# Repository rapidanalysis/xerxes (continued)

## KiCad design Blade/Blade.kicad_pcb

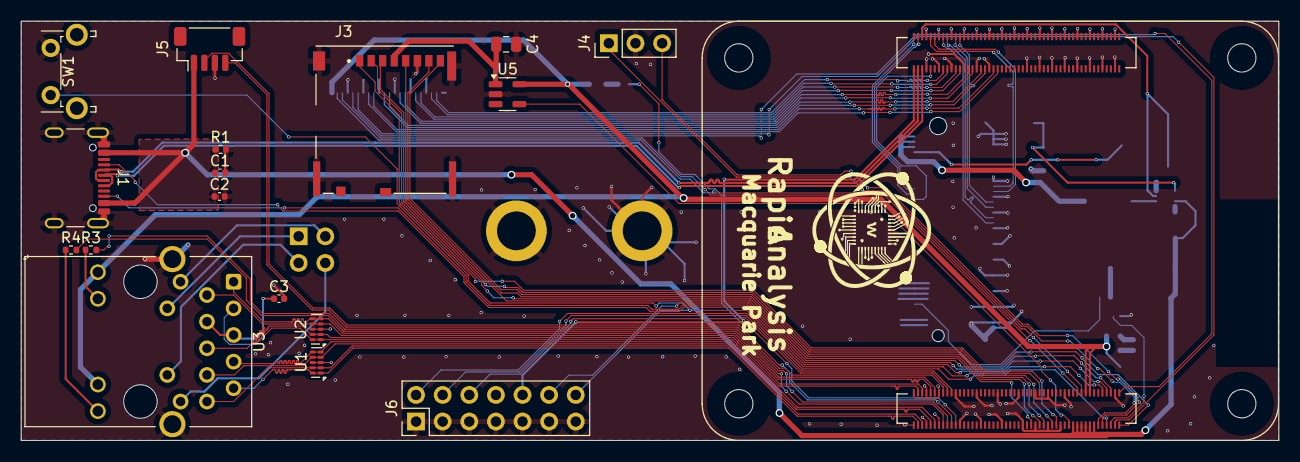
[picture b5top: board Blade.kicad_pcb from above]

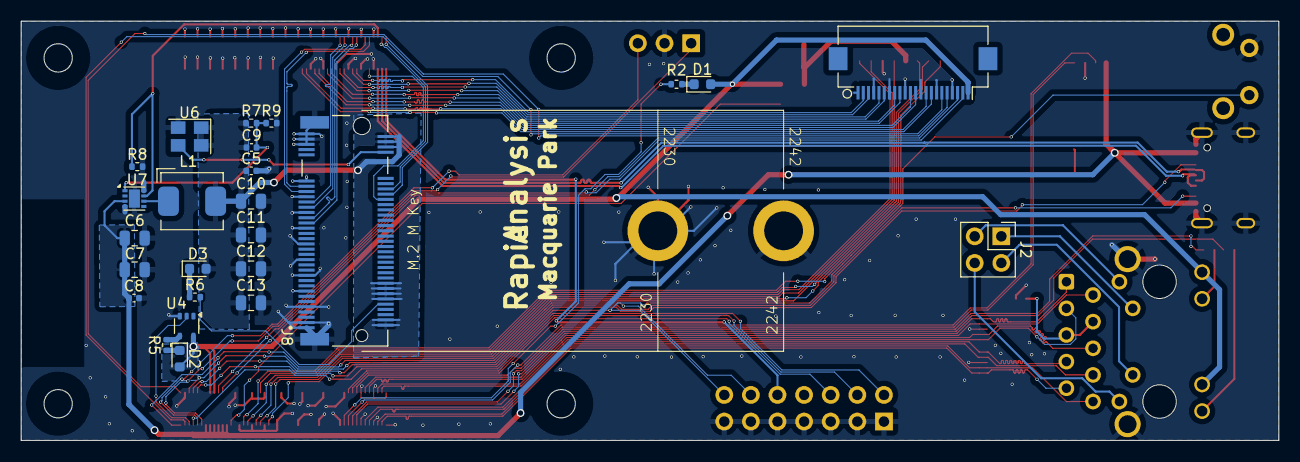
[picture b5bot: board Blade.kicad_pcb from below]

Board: 2 copper layers, 120.0 x 40.0 mm, 43 parts (25 on the bottom side), 77 nets.

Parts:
C1, C2, C3, C5, C8: 100n; C_0402_1005Metric
C4, C6, C7, C10, C11, C12, C13: 10u; C_0805_2012Metric
C9: 4.7nF; C_0402_1005Metric
D1, D3: LED Green; LED_0603_1608Metric
D2: LED Red; LED_0603_1608Metric
J1: USB_C_Receptacle_USB2.0; USB_C_Receptacle_GCT_USB4105-xx-A_16P_TopMnt_Horizontal
J2: THD-02-R; PinHeader_2x02_P2.54mm_Vertical
J3: Micro_SD_Card_Det; SDCARD_MOLEX_503398-1892
J4: Conn_01x03; PinHeader_1x03_P2.54mm_Vertical
J5: JST_SHBM04B-SRSS-TB; JST_SH_BM04B-SRSS-TB_1x04-1MP_P1.00mm_Vertical
J6: Conn_02x07_Odd_Even; PinHeader_2x07_P2.54mm_Vertical
J7: Conn_01x22_Female; Hirose_FH12-22S-0.5SH_1x22-1MP_P0.50mm_Horizontal
J8: Bus_M.2_Socket_M; M.2 M Key socket
L1: 2.2uH; L_Bourns_SRP5030CC
Module1: ComputeModule5-CM5; Raspberry-Pi-5-Compute-Module
R1, R9: 2.2K 1%; R_0402_1005Metric
R2, R5, R6: 1k; R_0402_1005Metric
R3, R4: 470R; R_0402_1005Metric
R7: 10K 1%; R_0402_1005Metric
R8: 100K 1%; R_0402_1005Metric
SW1: Right angle Tact button; SW_Tactile_SPST_Angled_PTS645Vx58-2LFS
U1, U2: TPD4EUSB30; USON-10_2.5x1.0mm_P0.5mm
U3: MagJack-A70-112-331N126; TRJG0926HENL
U4: 74LVC1G07SE-7; SOT-353_SC-70-5
U5: RT9742GGJ5; SOT-23-5
U6: ASEK-32.768KHZ-L-R-T; Crystal_SMD_3225-4Pin_3.2x2.5mm
U7: AP3441SHE-7B; DFN-8-1EP_2x2mm_P0.5mm_EP1.05x1.75mm

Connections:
/+3.3v: D1.2 (A), D2.2 (A), J7.22, Module1.84 (+3.3v_(Output)), Module1.86 (+3.3v_(Output)), U3.15 (LEDY_A), U3.17 (LEDG_A), U4.5 (VCC), U5.5 (IN)
/+5v: C1.1, C2.1, C6.1, C7.1, C8.1, J1.A4 (VBUS), J1.A9 (VBUS), J1.B4 (VBUS), J1.B9 (VBUS), J5.1, Module1.77 (+5v_(Input)), Module1.79 (+5v_(Input)), Module1.81 (+5v_(Input)), Module1.83 (+5v_(Input)), Module1.85 (+5v_(Input)), Module1.87 (+5v_(Input)), R1.1, U7.3 (VIN)
/CC1: J1.A5 (CC1), Module1.94 (CC1)
/CC2: J1.B5 (CC2), Module1.96 (CC2)
/CM5_GPIO ( Ethernet, GPIO, SDCARD)/BT_nDis: J4.3, Module1.91 (BT_nDisable)
/CM5_GPIO ( Ethernet, GPIO, SDCARD)/CAM_GPIO0: J7.17, Module1.97 (CAM_GPIO0)
/CM5_GPIO ( Ethernet, GPIO, SDCARD)/CAM_GPIO1: J7.18, Module1.100 (CAM_GPIO1)
/CM5_GPIO ( Ethernet, GPIO, SDCARD)/EEPROM_nWP: J6.4, Module1.20 (EEPROM_nWP)
/CM5_GPIO ( Ethernet, GPIO, SDCARD)/ETH_LEDG: Module1.17 (Ethernet_nLED2(3.3v)), R3.2
/CM5_GPIO ( Ethernet, GPIO, SDCARD)/ETH_LEDY: Module1.15 (Ethernet_nLED3(3.3v)), R4.2
/CM5_GPIO ( Ethernet, GPIO, SDCARD)/PMIC_ENABLE: J6.12, Module1.99 (PMIC_ENABLE)
/CM5_GPIO ( Ethernet, GPIO, SDCARD)/PWM: J5.2, Module1.19 (FAN_PWM)
/CM5_GPIO ( Ethernet, GPIO, SDCARD)/PWR_BUT: J6.14, Module1.92 (PWR_BUT), SW1.1
/CM5_GPIO ( Ethernet, GPIO, SDCARD)/SD_CLK: J3.5 (CLK), Module1.57 (SD_CLK)
/CM5_GPIO ( Ethernet, GPIO, SDCARD)/SD_CMD: J3.3 (CMD), Module1.62 (SD_CMD)
/CM5_GPIO ( Ethernet, GPIO, SDCARD)/SD_DAT0: J3.7 (DAT0), Module1.63 (SD_DAT0)
/CM5_GPIO ( Ethernet, GPIO, SDCARD)/SD_DAT1: J3.8 (DAT1), Module1.67 (SD_DAT1)
/CM5_GPIO ( Ethernet, GPIO, SDCARD)/SD_DAT2: J3.1 (DAT2), Module1.69 (SD_DAT2)
/CM5_GPIO ( Ethernet, GPIO, SDCARD)/SD_DAT3: J3.2 (DAT3/CD), Module1.61 (SD_DAT3)
/CM5_GPIO ( Ethernet, GPIO, SDCARD)/SD_PWR: C4.1, J3.4 (VDD), U5.1 (OUT)
/CM5_GPIO ( Ethernet, GPIO, SDCARD)/SD_PWR_ON: Module1.75 (SD_PWR_ON), U5.4 (EN)
/CM5_GPIO ( Ethernet, GPIO, SDCARD)/SYNC_OUT: J6.6, Module1.18 (Ethernet_SYNC_OUT(3.3v))
/CM5_GPIO ( Ethernet, GPIO, SDCARD)/TACHO: J5.4, Module1.16 (FAN_TACHO)
/CM5_GPIO ( Ethernet, GPIO, SDCARD)/TR0_TAP: J2.3, U3.11 (VC1)
/CM5_GPIO ( Ethernet, GPIO, SDCARD)/TR1_TAP: J2.1, U3.12 (VC2)
/CM5_GPIO ( Ethernet, GPIO, SDCARD)/TR2_TAP: J2.2, U3.13 (VC3)
/CM5_GPIO ( Ethernet, GPIO, SDCARD)/TR3_TAP: J2.4, U3.14 (VC4)
/CM5_GPIO ( Ethernet, GPIO, SDCARD)/TRD0_N: Module1.10 (Ethernet_Pair0_N), U2.4 (D2+), U2.7, U3.2 (TRD0-)
/CM5_GPIO ( Ethernet, GPIO, SDCARD)/TRD0_P: Module1.12 (Ethernet_Pair0_P), U2.5 (D2-), U2.6, U3.1 (TRD0+)
/CM5_GPIO ( Ethernet, GPIO, SDCARD)/TRD1_N: Module1.6 (Ethernet_Pair1_N), U2.2 (D1-), U2.9, U3.6 (TRD1-)
/CM5_GPIO ( Ethernet, GPIO, SDCARD)/TRD1_P: Module1.4 (Ethernet_Pair1_P), U2.1 (D1+), U2.10, U3.3 (TRD1+)
/CM5_GPIO ( Ethernet, GPIO, SDCARD)/TRD2_N: Module1.9 (Ethernet_Pair2_N), U1.4 (D2+), U1.7, U3.8 (TRD2-)
/CM5_GPIO ( Ethernet, GPIO, SDCARD)/TRD2_P: Module1.11 (Ethernet_Pair2_P), U1.5 (D2-), U1.6, U3.7 (TRD2+)
/CM5_GPIO ( Ethernet, GPIO, SDCARD)/TRD3_N: Module1.5 (Ethernet_Pair3_N), U1.2 (D1-), U1.9, U3.10 (TRD3-)
/CM5_GPIO ( Ethernet, GPIO, SDCARD)/TRD3_P: Module1.3 (Ethernet_Pair3_P), U1.1 (D1+), U1.10, U3.9 (TRD3+)
/CM5_GPIO ( Ethernet, GPIO, SDCARD)/USBOTG: J6.10, Module1.101 (USB_OTG_ID)
/CM5_GPIO ( Ethernet, GPIO, SDCARD)/WL_nDis: J4.1, Module1.89 (WiFi_nDisable)
/CM5_GPIO ( Ethernet, GPIO, SDCARD)/nPWR_LED: Module1.95 (LED_nPWR), U4.2
/CM5_GPIO ( Ethernet, GPIO, SDCARD)/nRPIBOOT: J6.2, Module1.93 (nRPIBOOT)
/CM5_HighSpeed/DPHY0_C_N: J7.8, Module1.127 (MIPI0_C_N)
/CM5_HighSpeed/DPHY0_C_P: J7.9, Module1.129 (MIPI0_C_P)
/CM5_HighSpeed/DPHY0_D0_N: J7.2, Module1.115 (MIPI0_D0_N)
/CM5_HighSpeed/DPHY0_D0_P: J7.3, Module1.117 (MIPI0_D0_P)
/CM5_HighSpeed/DPHY0_D1_N: J7.5, Module1.121 (MIPI0_D1_N)
/CM5_HighSpeed/DPHY0_D1_P: J7.6, Module1.123 (MIPI0_D1_P)
/CM5_HighSpeed/DPHY0_D2_N: J7.11, Module1.133 (MIPI0_D2_N)
/CM5_HighSpeed/DPHY0_D2_P: J7.12, Module1.135 (MIPI0_D2_P)
/CM5_HighSpeed/DPHY0_D3_N: J7.14, Module1.139 (MIPI0_D3_N)
/CM5_HighSpeed/DPHY0_D3_P: J7.15, Module1.141 (MIPI0_D3_P)
/CM5_HighSpeed/PCIE_CLK_N: J8.53 (REFCLKn), Module1.112 (PCIe_CLK_N)
/CM5_HighSpeed/PCIE_CLK_P: J8.55 (REFCLKp), Module1.110 (PCIe_CLK_P)
/CM5_HighSpeed/PCIE_PWR_EN: Module1.106 (PCIE_PWR_EN), R8.1, U7.7 (EN)
/CM5_HighSpeed/PCIE_RX_N: J8.43 (PETp0), Module1.118 (PCIe_RX_N)
/CM5_HighSpeed/PCIE_RX_P: J8.41 (PETn0), Module1.116 (PCIe_RX_P)
/CM5_HighSpeed/PCIE_TX_N: J8.49 (PERp0), Module1.124 (PCIe_TX_N)
/CM5_HighSpeed/PCIE_TX_P: J8.47 (PERn0), Module1.122 (PCIe_TX_P)
/CM5_HighSpeed/PCIE_nCLKREQ: J8.52 (~CLKREQ), Module1.102 (PCIe_nCLKREQ)
/CM5_HighSpeed/PCIE_nRST: J8.50 (~PERST), Module1.109 (PCIe_nRST)
/CM5_HighSpeed/PCIE_nWAKE: J8.54 (~PEWAKE), Module1.104 (PCIE_nWAKE)
/CM5_HighSpeed/SCL0: J7.20, Module1.80 (SCL0)
/CM5_HighSpeed/SDA0: J7.21, Module1.82 (SDA0)
/PCIe-M2/FB: C9.2, R7.2, R9.1, U7.1 (FB)
/PCIe-M2/M2_3v3: C5.1, C9.1, C10.1, C11.1, C12.1, C13.1, D3.2 (A), J8.2 (3.3V), J8.4 (3.3V), J8.12 (3.3V), J8.14 (3.3V), J8.16 (3.3V), J8.18 (3.3V), J8.70 (3.3V), J8.72 (3.3V), J8.74 (3.3V), L1.2, R7.1, U6.1 (EN), U6.4 (VDD)
/USB2_N: J1.A7 (D-), J1.B7 (D-), Module1.103 (USB2_N)
/USB2_P: J1.A6 (D+), J1.B6 (D+), Module1.105 (USB2_P)
GND: C1.2, C2.2, C3.2, C4.2, C5.2, C6.2, C7.2, C8.2, C10.2, C11.2, C12.2, C13.2, J1.A1 (GND), J1.A12 (GND), J1.B1 (GND), J1.B12 (GND), J1.S1 (SHIELD), J3.6 (VSS), J3.11 (SHIELD), J4.2, J5.3, J6.1, J6.3, J6.5, J6.7, J6.9, J6.11, J6.13, J7.1, J7.4, J7.7, J7.10, J7.13, J7.16, J7.19, J8.1 (GND), J8.3 (GND), J8.9 (GND), J8.15 (GND), J8.21 (GND), J8.27 (GND), J8.33 (GND), J8.39 (GND), J8.45 (GND), J8.51 (GND), J8.57 (GND), J8.71 (GND), J8.73 (GND), J8.75 (GND), J8.M1 (GND2230), J8.M2 (GND2242), J8.S1, J8.S2, Module1.1 (GND), Module1.2 (GND), Module1.7 (GND), Module1.8 (GND), Module1.13 (GND), Module1.14 (GND), Module1.22 (GND), Module1.23 (GND), Module1.32 (GND), Module1.33 (GND), Module1.42 (GND), Module1.43 (GND), Module1.52 (GND), Module1.53 (GND), Module1.59 (GND), Module1.60 (GND), Module1.65 (GND), Module1.66 (GND), Module1.71 (GND), Module1.74 (GND), Module1.98 (GND), Module1.107 (GND), Module1.108 (GND), Module1.113 (GND), Module1.114 (GND), Module1.119 (GND), Module1.120 (GND), Module1.125 (GND), Module1.126 (GND), Module1.131 (GND), Module1.132 (GND), Module1.137 (GND), Module1.138 (GND), Module1.144 (GND), Module1.150 (GND), Module1.155 (GND), Module1.156 (GND), Module1.161 (GND), Module1.162 (GND), Module1.167 (GND), Module1.168 (GND), Module1.173 (GND), Module1.174 (GND), Module1.179 (GND), Module1.180 (GND), Module1.185 (GND), Module1.186 (GND), Module1.191 (GND), Module1.192 (GND), Module1.197 (GND), Module1.198 (GND), R1.2, R8.2, R9.2, SW1.2, U1.3 (GND), U1.8 (GND), U2.3 (GND), U2.8 (GND), U3.19 (SHIELD), U3.20 (SHIELD), U4.3 (GND), U5.2 (GND), U6.2 (GND), U7.4 (PGND), U7.8 (SGND), U7.9 (PAD)
unnamed: C3.1, U3.4 (CT), U3.5 (CT)
unnamed: D1.1 (K), R2.1
unnamed: D2.1 (K), R5.1
unnamed: D3.1 (K), R6.1
unnamed: J8.10 (DAS/~DSS/~LED1), R6.2
unnamed: J8.68 (SUSCLK), U6.3 (Out)
unnamed: Module1.21 (LED_nACT), R2.2
unnamed: R5.2, U4.4
unnamed: R4.1, U3.18 (LEDG_K)
unnamed: R3.1, U3.16 (LEDY_K)
unnamed: L1.1, U7.6 (LX)

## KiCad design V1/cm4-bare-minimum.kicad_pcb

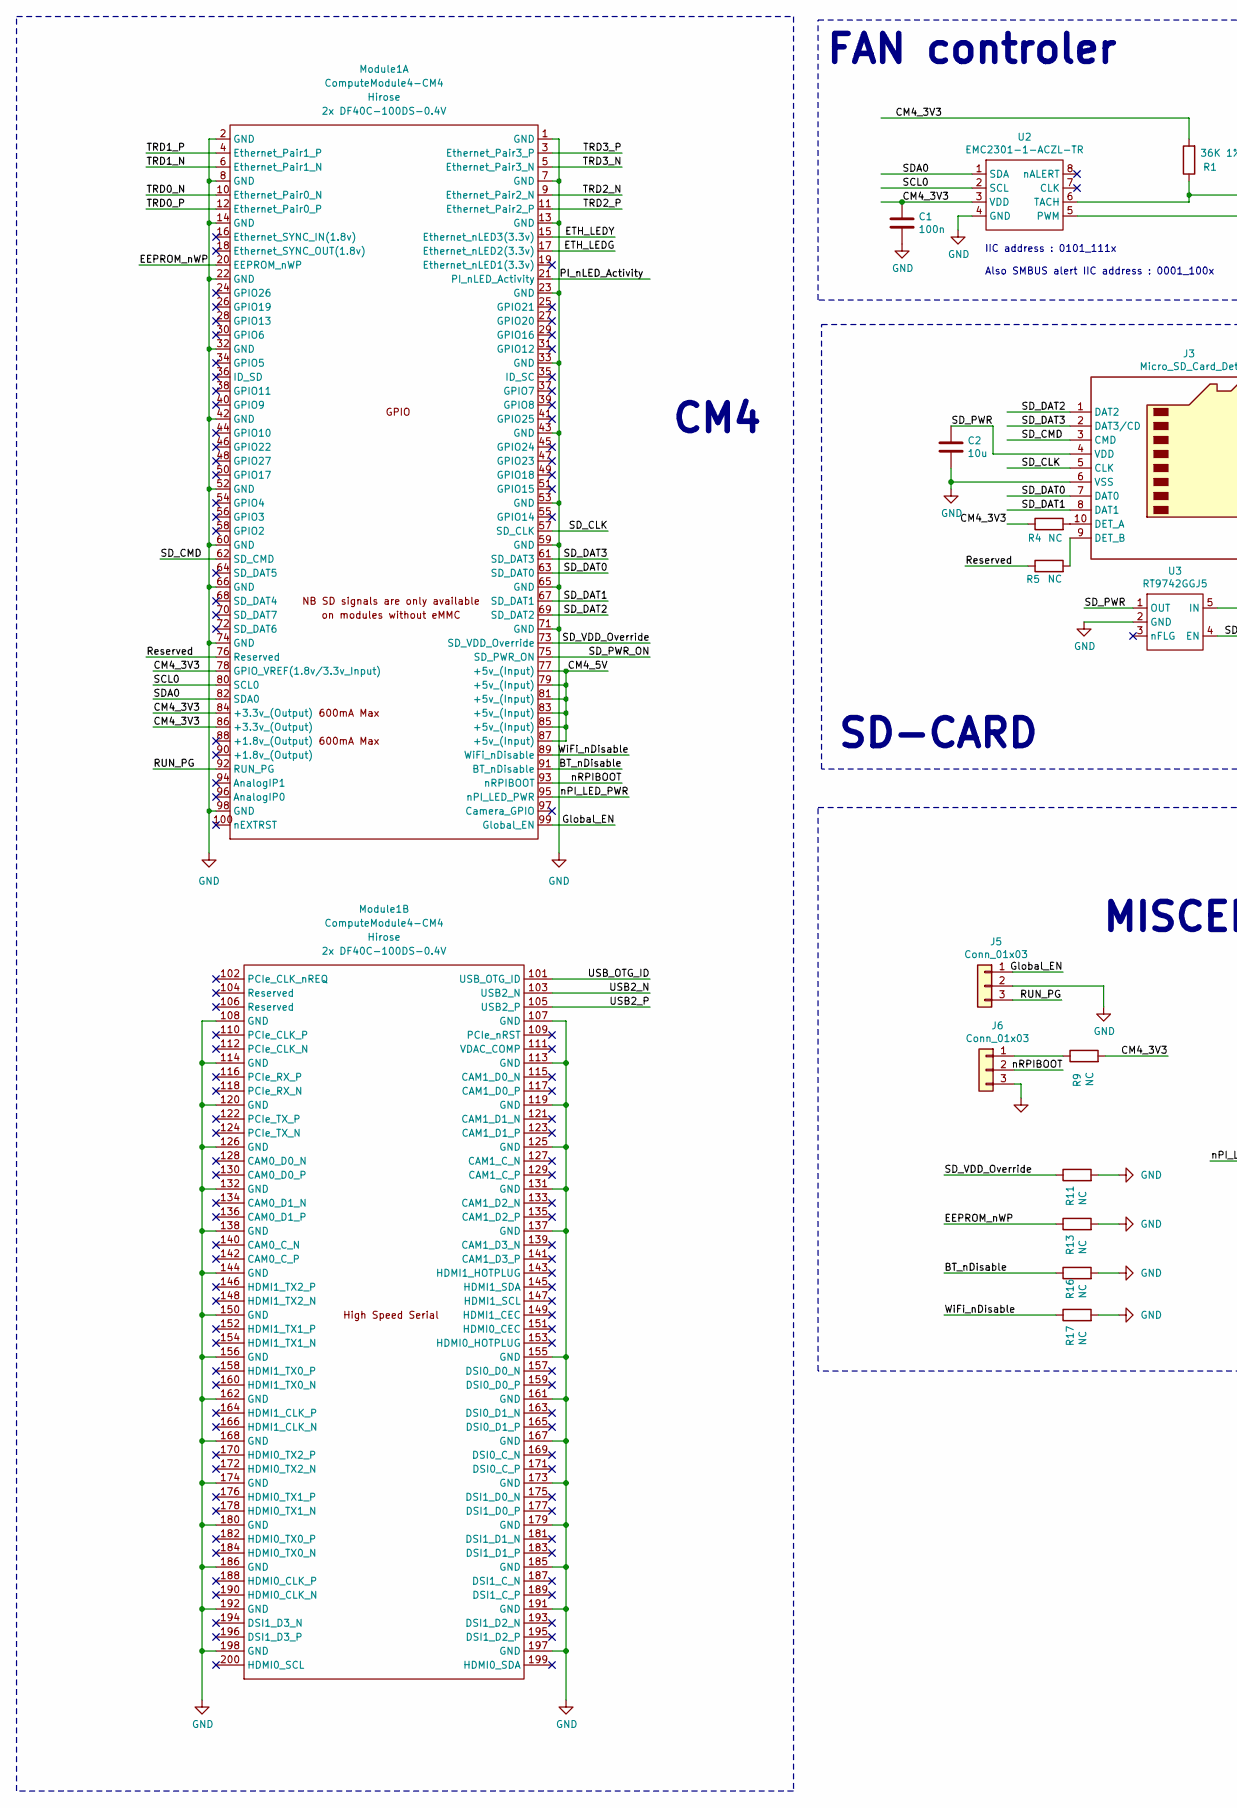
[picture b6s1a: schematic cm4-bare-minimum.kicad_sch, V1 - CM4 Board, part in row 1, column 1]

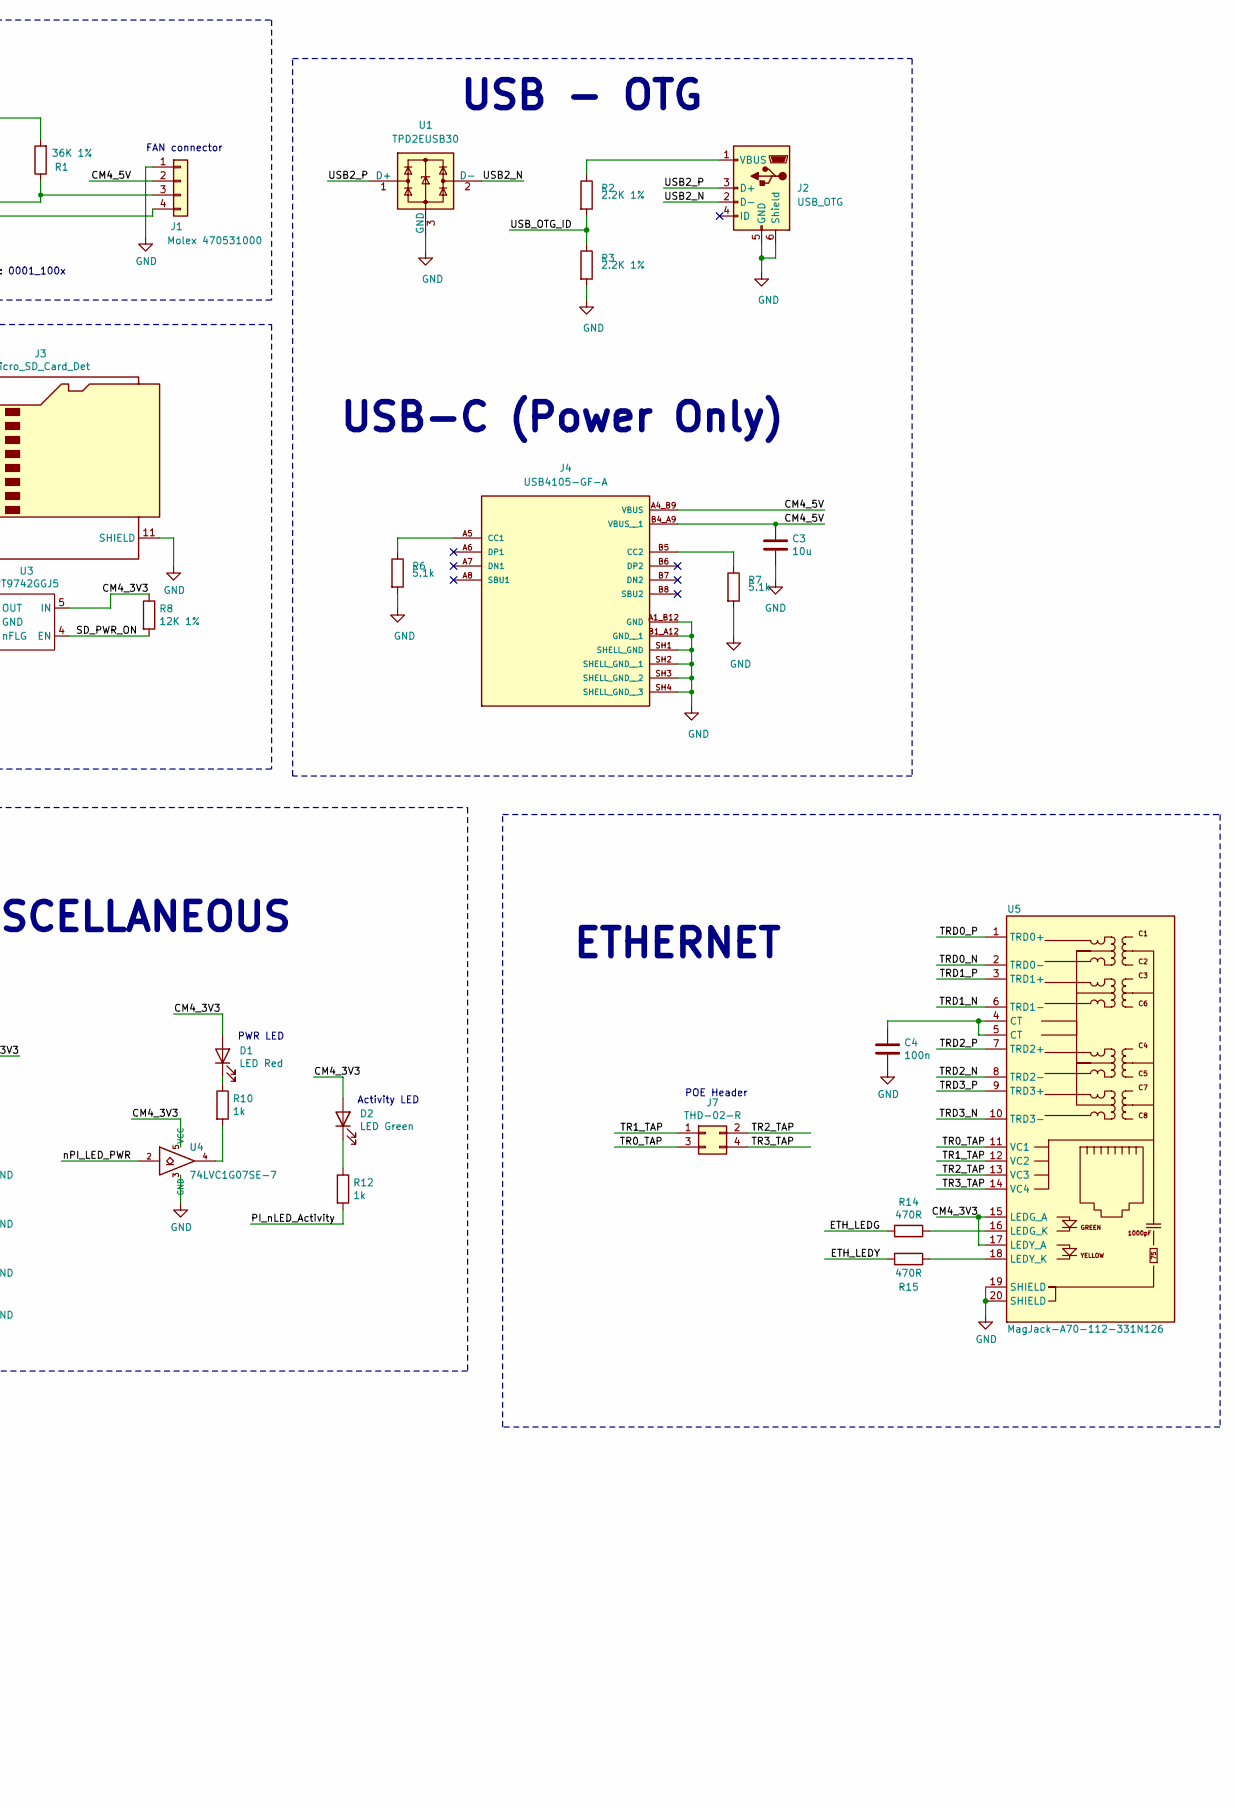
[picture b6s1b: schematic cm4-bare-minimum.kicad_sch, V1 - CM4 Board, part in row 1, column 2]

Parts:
C1, C4: 100n; C_0402_1005Metric; Part Description 0.1uF 10% 16V Ceramic Capacitor X7R 040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
C2, C3: 10u; C_0805_2012Metric; Part Description 10uF 10% 10V Ceramic Capacitor X7R 0805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
D1: LED Red; LED_0603_1608Metric; Part Description Red 620nm LED Indication - Discrete 2.2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
D2: LED Green; LED_0603_1608Metric; Part Description Green 572nm LED Indication - Discrete 2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
J1: Molex 470531000; FanPinHeader_1x04_P2.54mm_Vertical; Part Description Connector Header Through Hole 4 positio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
J2: USB_OTG; USB_Micro-B_EDAC_UCON00686; MPN 10103594-0001LF; Digi-Key_PN 609-4050-1-ND
J3: Micro_SD_Card_Det; SDCARD_MOLEX_503398-1892; Part Description 9 (8 + 1) Position Card Connector micro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
J4: USB4105-GF-A; GCT_USB4105-GF-A; PARTREV B4
J5, J6: Conn_01x03; PinHeader_1x03_P2.54mm_Vertical; Part Description 3pin 0.1" connector
J7: THD-02-R; PinHeader_2x02_P2.54mm_Vertical; Part Description PinHeader_2x02_P2.54mm_Vertical
Module1: ComputeModule4-CM4; Raspberry-Pi-4-Compute-Module
R1: 36K 1%; R_0402_1005Metric; Part Description Resistor 36K M1005 1% 63mW
R2, R3: 2.2K 1%; R_0603_1608Metric_Pad0.98x0.95mm_HandSolder; MPN RC0603FR-072K2L; Digi-Key_PN 311-2.20KHRCT-ND
R4, R5: NC; R_0402_1005Metric; Part Description Resistor 1K M1005 1% 63mW
R6, R7: 5.1k; R_0603_1608Metric_Pad0.98x0.95mm_HandSolder; MPN RC0603FR-075K1L; Digi-Key_PN 311-5.10KHRCT-ND
R8: 12K 1%; R_0402_1005Metric; Part Description Resistor 12K M1005 1% 63mW
R9, R11, R13, R16, R17: NC; R_0402_1005Metric; Part Description Resistor 2.2K M1005 1% 63mW
R10, R12: 1k; R_0402_1005Metric; Part Description Resistor 1K M1005 1% 63mW
R14, R15: 470R; R_0402_1005Metric; Part Description Resistor 470R M1005 1% 63mW
U1: TPD2EUSB30; Texas_DRT-3; MPN TPD2EUSB30DRTR; Digi-Key_PN 296-25509-1-ND
U2: EMC2301-1-ACZL-TR; MSOP-8_3x3mm_P0.65mm; Part Description Motor Driver PWM 8-MSOP
U3: RT9742GGJ5; SOT-23-5; Part Description Power Switch/Driver 1:1 N-Channel 1A TS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
U4: 74LVC1G07SE-7; SOT-353_SC-70-5; Part Description Buffer, Non-Inverting 1 Element 1 Bit p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
U5: MagJack-A70-112-331N126; TRJG0926HENL; Part Description Gigabit Ethernet Magjack

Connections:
/BT_nDisable: Module1.91 (BT_nDisable), R16.1
/CM4_3V3: C1.1, D1.2 (A), D2.2 (A), Module1.78 (GPIO_VREF(1.8v/3.3v_Input)), Module1.84 (+3.3v_(Output)), Module1.86 (+3.3v_(Output)), R1.2, R4.1, R8.1, R9.2, U2.3 (VDD), U3.5 (IN), U4.5 (VCC), U5.15 (LEDG_A), U5.17 (LEDY_A)
/CM4_5V: C3.1, J1.2, J4.A4_B9 (VBUS), J4.B4_A9 (VBUS__1), Module1.77 (+5v_(Input)), Module1.79 (+5v_(Input)), Module1.81 (+5v_(Input)), Module1.83 (+5v_(Input)), Module1.85 (+5v_(Input)), Module1.87 (+5v_(Input))
/EEPROM_nWP: Module1.20 (EEPROM_nWP), R13.1
/ETH_LEDG: Module1.17 (Ethernet_nLED2(3.3v)), R14.2
/ETH_LEDY: Module1.15 (Ethernet_nLED3(3.3v)), R15.2
/Global_EN: J5.1, Module1.99 (Global_EN)
/RUN_PG: J5.3, Module1.92 (RUN_PG)
/Reserved: Module1.76 (Reserved), R5.1
/SCL0: Module1.80 (SCL0), U2.2 (SCL)
/SDA0: Module1.82 (SDA0), U2.1 (SDA)
/SD_CLK: J3.5 (CLK), Module1.57 (SD_CLK)
/SD_CMD: J3.3 (CMD), Module1.62 (SD_CMD)
/SD_DAT0: J3.7 (DAT0), Module1.63 (SD_DAT0)
/SD_DAT1: J3.8 (DAT1), Module1.67 (SD_DAT1)
/SD_DAT2: J3.1 (DAT2), Module1.69 (SD_DAT2)
/SD_DAT3: J3.2 (DAT3/CD), Module1.61 (SD_DAT3)
/SD_PWR: C2.1, J3.4 (VDD), U3.1 (OUT)
/SD_PWR_ON: Module1.75 (SD_PWR_ON), R8.2, U3.4 (EN)
/SD_VDD_Override: Module1.73 (SD_VDD_Override), R11.1
/TR0_TAP: J7.3, U5.11 (VC1)
/TR1_TAP: J7.1, U5.12 (VC2)
/TR2_TAP: J7.2, U5.13 (VC3)
/TR3_TAP: J7.4, U5.14 (VC4)
/TRD0_N: Module1.10 (Ethernet_Pair0_N), U5.2 (TRD0-)
/TRD0_P: Module1.12 (Ethernet_Pair0_P), U5.1 (TRD0+)
/TRD1_N: Module1.6 (Ethernet_Pair1_N), U5.6 (TRD1-)
/TRD1_P: Module1.4 (Ethernet_Pair1_P), U5.3 (TRD1+)
/TRD2_N: Module1.9 (Ethernet_Pair2_N), U5.8 (TRD2-)
/TRD2_P: Module1.11 (Ethernet_Pair2_P), U5.7 (TRD2+)
/TRD3_N: Module1.5 (Ethernet_Pair3_N), U5.10 (TRD3-)
/TRD3_P: Module1.3 (Ethernet_Pair3_P), U5.9 (TRD3+)
/USB2_N: J2.2 (D-), Module1.103 (USB2_N), U1.2 (D-)
/USB2_P: J2.3 (D+), Module1.105 (USB2_P), U1.1 (D+)
/USB_OTG_ID: Module1.101 (USB_OTG_ID), R2.2, R3.1
/WiFi_nDisable: Module1.89 (WiFi_nDisable), R17.1
/nPI_LED_PWR: Module1.95 (nPI_LED_PWR), U4.2
/nRPIBOOT: J6.2, Module1.93 (nRPIBOOT)
unnamed: C4.1, U5.4 (CT), U5.5 (CT)
unnamed: D1.1 (K), R10.1
unnamed: D2.1 (K), R12.1
unnamed: J1.3, R1.1, U2.6 (TACH)
unnamed: J1.4, U2.5 (PWM)
unnamed: J2.1 (VBUS), R2.1
unnamed: J3.10 (DET_A), R4.2
unnamed: J3.9 (DET_B), R5.2
unnamed: J4.A5 (CC1), R6.1
unnamed: J4.B5 (CC2), R7.1
unnamed: J6.1, R9.1
unnamed: R10.2, U4.4
unnamed: R14.1, U5.16 (LEDG_K)
unnamed: R15.1, U5.18 (LEDY_K)

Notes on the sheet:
USB-C (Power Only)
FAN controler
Activity LED
IIC address : 0101_111x
FAN connector
PWR LED
USB - OTG
POE Header
Also SMBUS alert IIC address : 0001_100x
MISCELLANEOUS
ETHERNET
CM4
SD-CARD

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
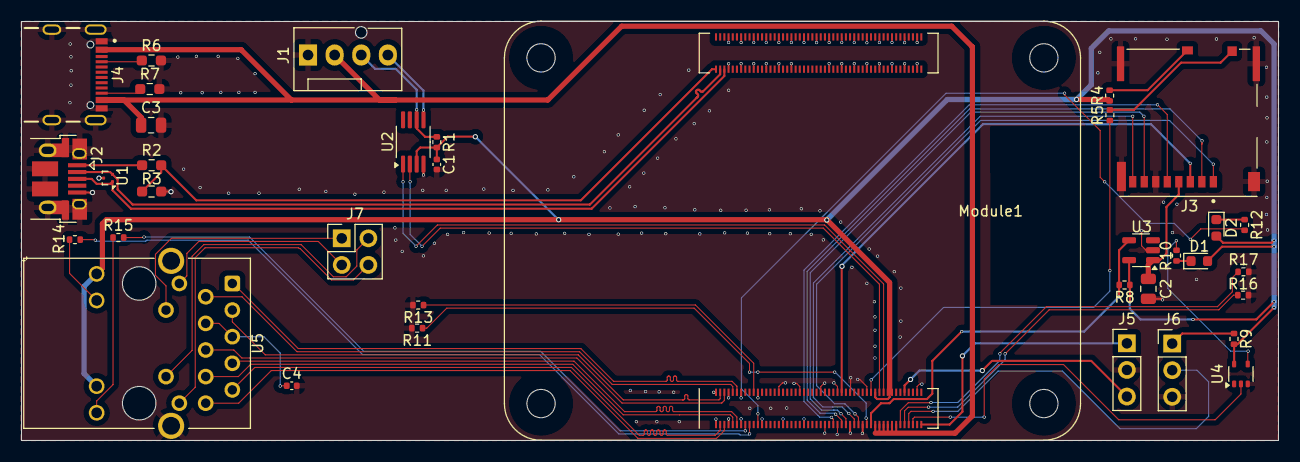
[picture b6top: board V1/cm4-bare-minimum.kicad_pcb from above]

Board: 2 copper layers, 120.0 x 40.0 mm, 36 parts (0 on the bottom side), 54 nets.
